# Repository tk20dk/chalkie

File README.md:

# chalkie
SPDIF Interface board for Wally sniffer

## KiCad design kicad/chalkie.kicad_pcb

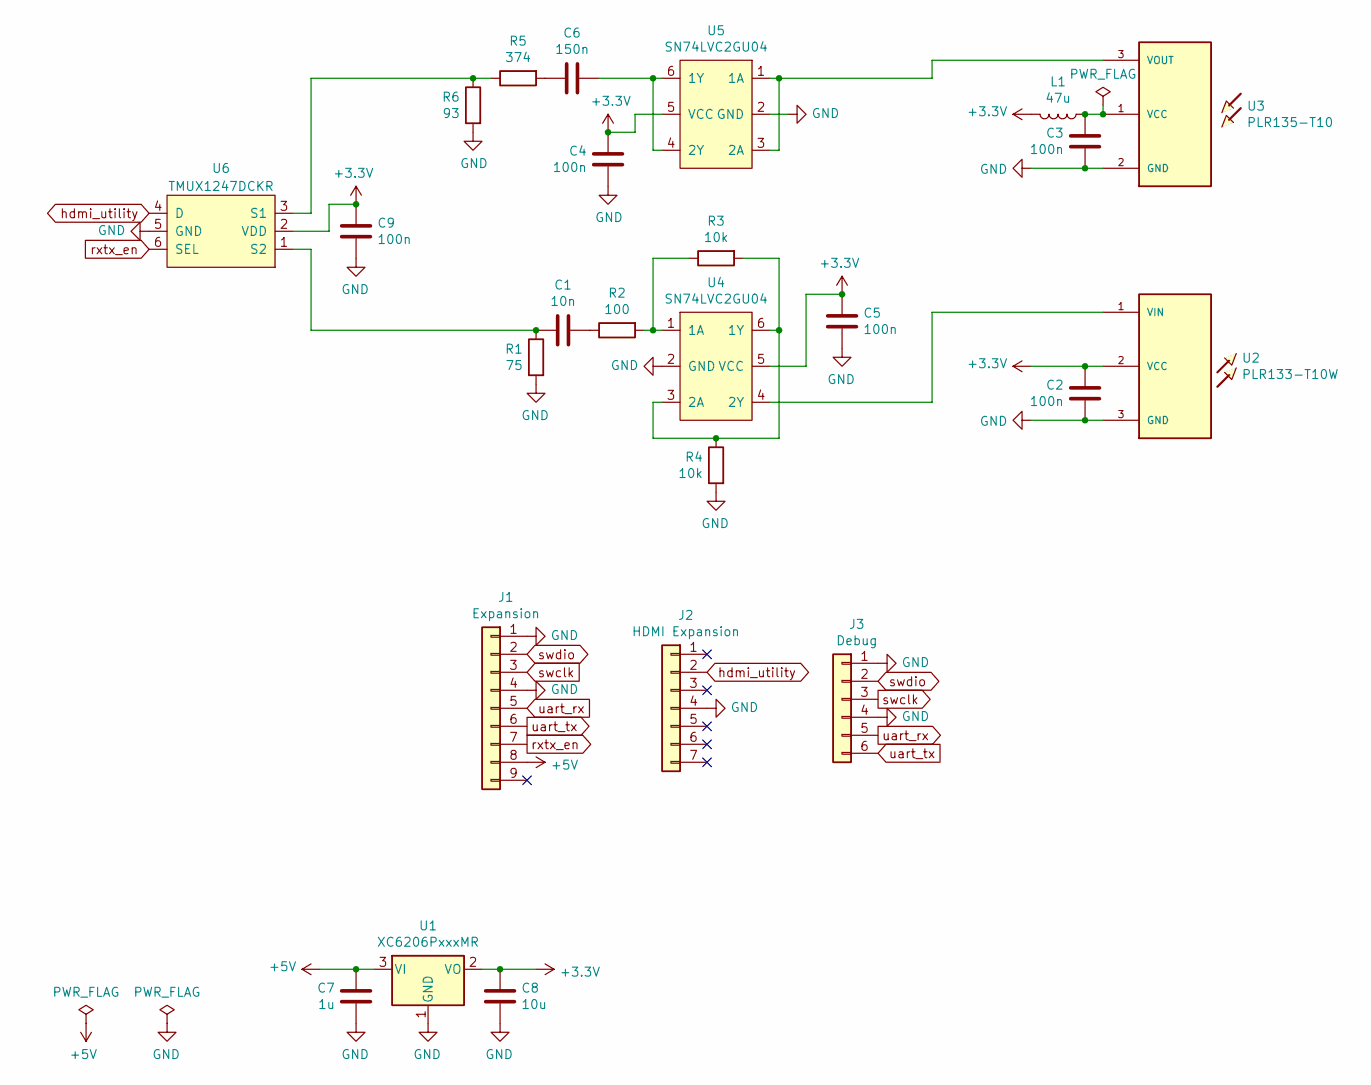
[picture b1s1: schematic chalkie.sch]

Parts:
C1: 10n; C_0603_1608Metric
C2, C3, C4, C5, C9: 100n; C_0603_1608Metric
C6: 150n; C_0603_1608Metric
C7: 1u; C_0805_2012Metric
C8: 10u; C_0805_2012Metric
J1: Expansion; PinSocket_1x09_P2.54mm_Vertical
J2: HDMI Expansion; PinSocket_1x07_P2.54mm_Vertical
J3: Debug; PinHeader_1x06_P2.54mm_Vertical
L1: 47u; L_0805_2012Metric
R1: 75; R_0603_1608Metric
R2: 100; R_0603_1608Metric
R3, R4: 10k; R_0603_1608Metric
R5: 374; R_0603_1608Metric
R6: 93; R_0603_1608Metric
U1: XC6206PxxxMR; SOT-23
U2: PLR133-T10W; PLT133T10W
U3: PLR135-T10; PLR135T10
U4, U5: SN74LVC2GU04; SOT-23-6
U6: TMUX1247DCKR; SOT65P210X110-6N

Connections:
+3V3: C2.2, C4.2, C5.2, C8.2, C9.2, L1.2, U1.2 (VO), U2.2 (VCC), U4.5 (VCC), U5.5 (VCC), U6.2 (VDD)
+5V: C7.2, J1.8, U1.3 (VI)
GND: C2.1, C3.1, C4.1, C5.1, C7.1, C8.1, C9.1, J1.1, J1.4, J2.4, J3.1, J3.4, R1.2, R4.2, R6.2, U1.1 (GND), U2.3 (GND), U3.2 (GND), U4.2 (GND), U5.2 (GND), U6.5 (GND)
unnamed: C1.1, R1.1, U6.1 (S2)
unnamed: C1.2, R2.1
unnamed: C3.2, L1.1, U3.1 (VCC)
unnamed: C6.1, R5.2
unnamed: C6.2, U5.4 (2Y), U5.6 (1Y)
unnamed: R2.2, R3.1, U4.1 (1A)
unnamed: R3.2, R4.1, U4.3 (2A), U4.6 (1Y)
unnamed: R5.1, R6.1, U6.3 (S1)
unnamed: U2.1 (VIN), U4.4 (2Y)
unnamed: U3.3 (VOUT), U5.1 (1A), U5.3 (2A)
hdmi_utility: J2.2, U6.4 (D)
rxtx_en: J1.7, U6.6 (SEL)
swclk: J1.3, J3.3
swdio: J1.2, J3.2
uart_rx: J1.5, J3.5
uart_tx: J1.6, J3.6

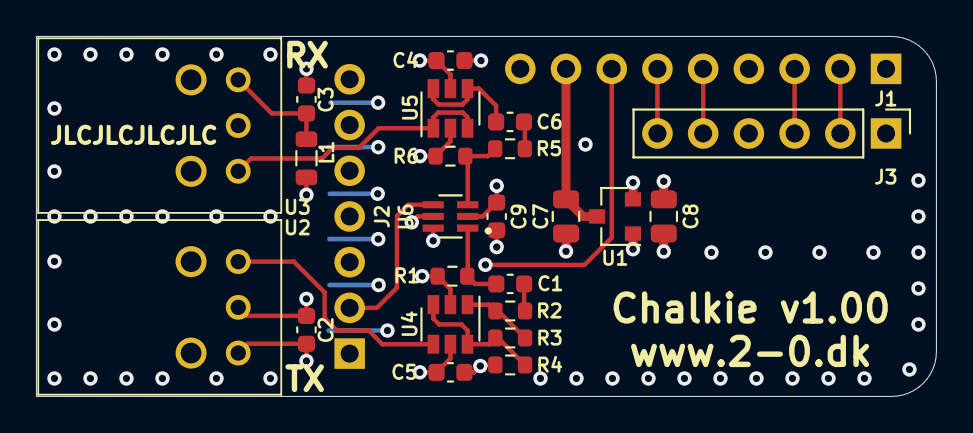
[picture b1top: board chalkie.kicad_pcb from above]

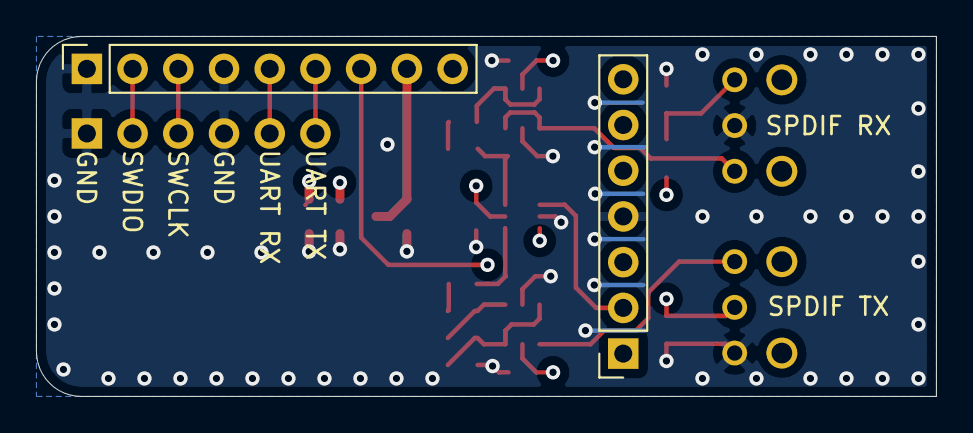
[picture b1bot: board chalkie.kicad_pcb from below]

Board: 4 copper layers, 50.0 x 20.0 mm, 25 parts (2 on the bottom side), 19 nets.

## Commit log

2021-08-01 Chalkie v1.00
